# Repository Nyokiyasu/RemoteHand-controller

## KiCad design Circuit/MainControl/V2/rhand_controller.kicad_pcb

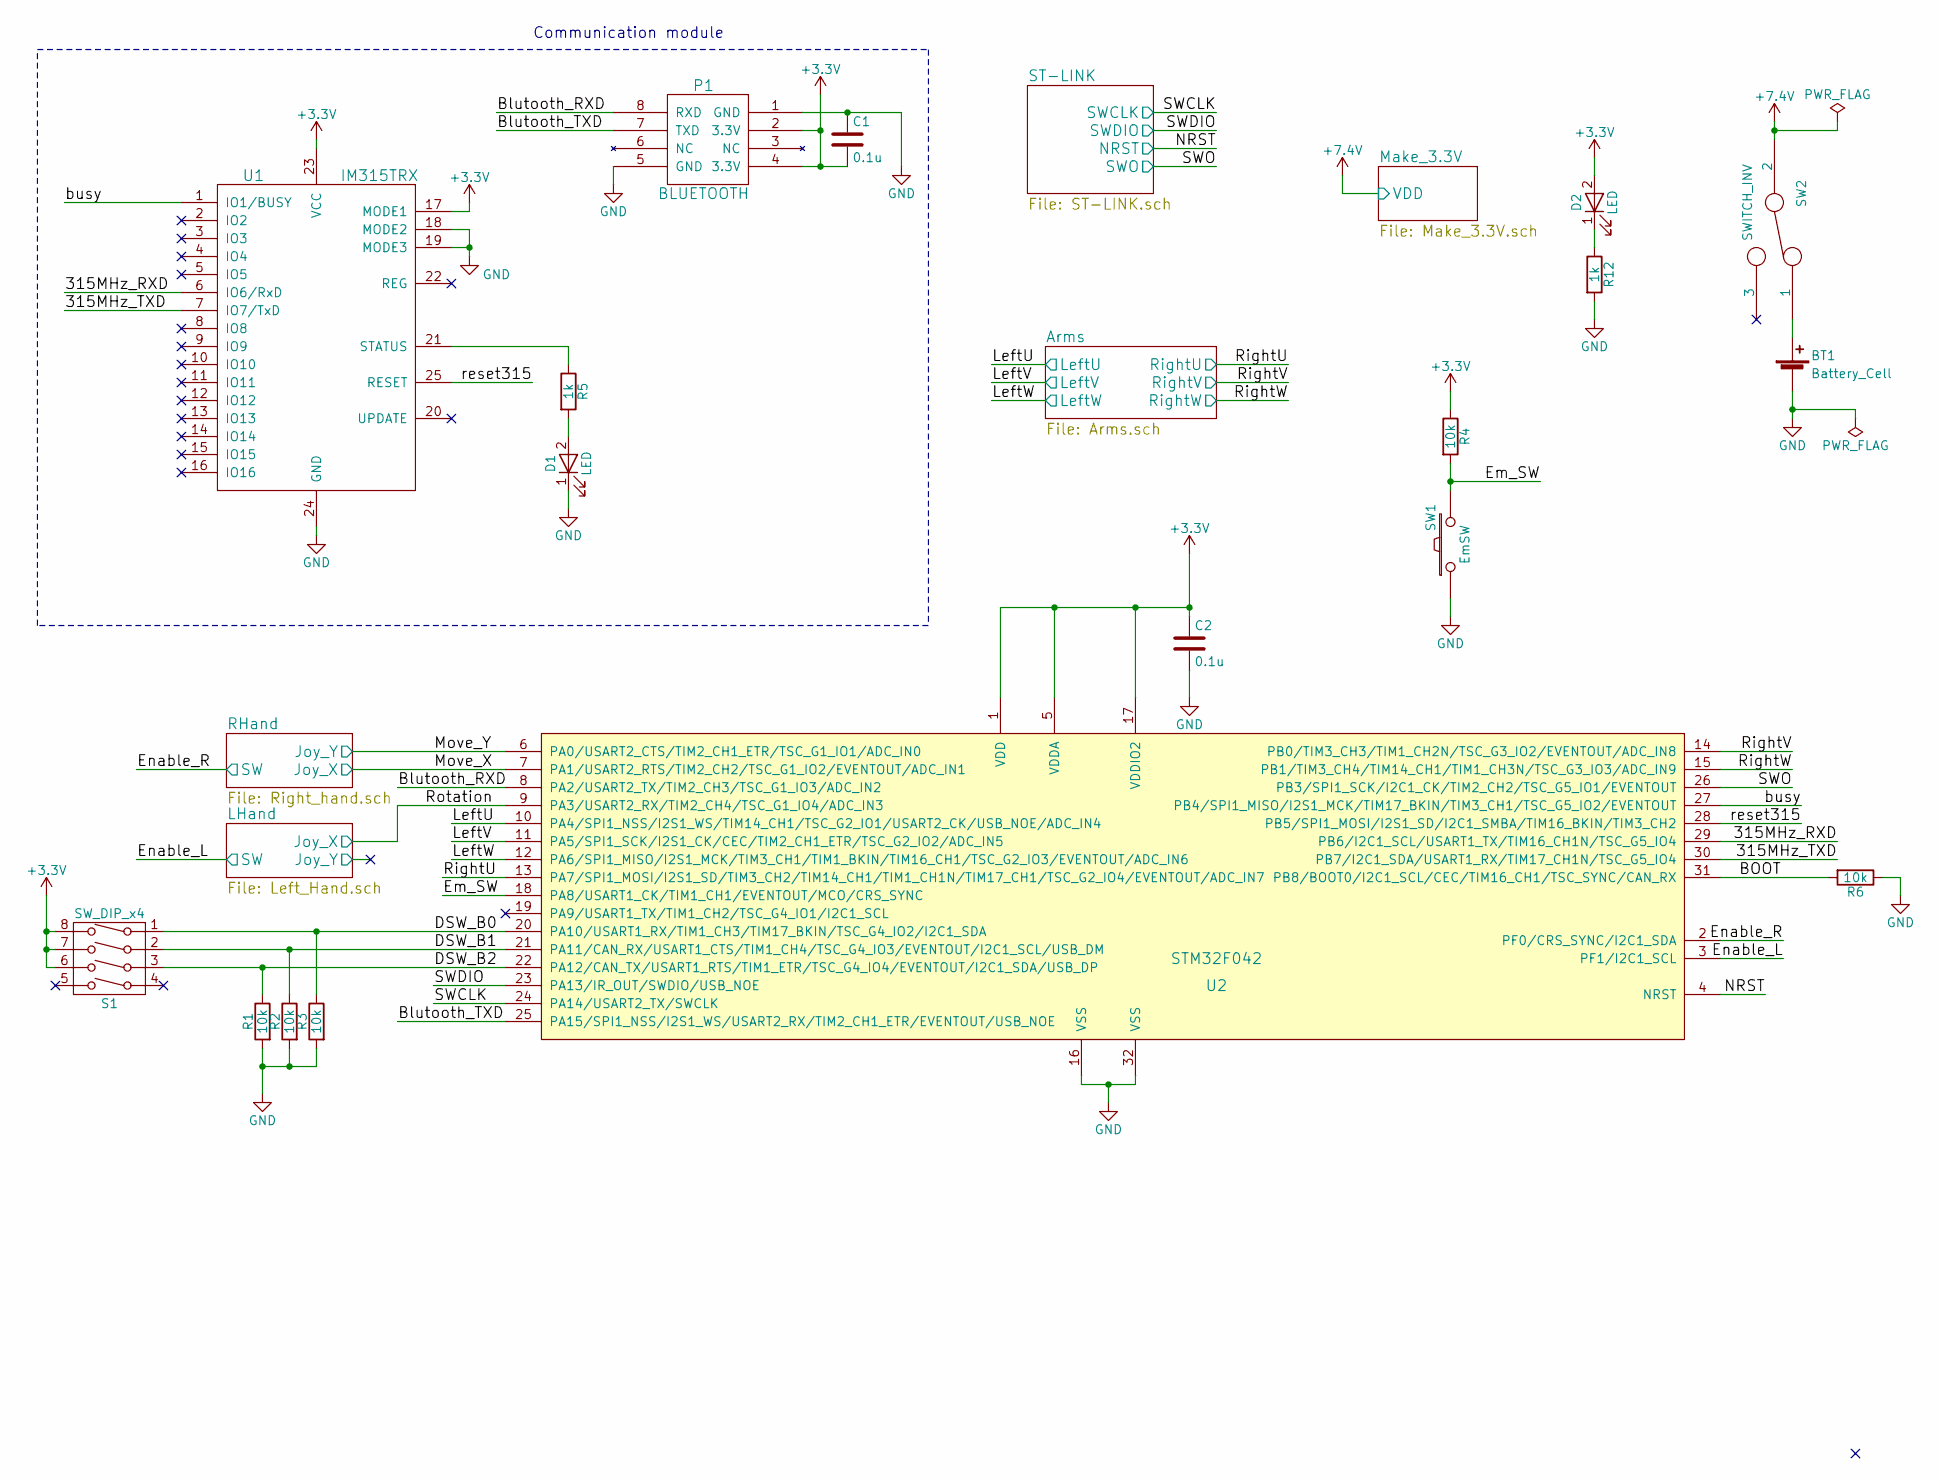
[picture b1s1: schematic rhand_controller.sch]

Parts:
BT1: Battery_Cell; XT_Mdot
C1, C2: 0.1u; C_0805_HandSoldering_LP
D1, D2: LED; LED_D5.0mm
P1: BLUETOOTH; ESD200
R1, R2, R3, R6: 10k; R_0603_HandSoldering_LP
R4: 10k; R_Axial_DIN0207_L6.3mm_D2.5mm_P7.62mm_Horizontal
R5, R12: 1k; R_Axial_DIN0207_L6.3mm_D2.5mm_P7.62mm_Horizontal
S1: SW_DIP_x4; SW_DIP_x4_W7.62mm_Slide
SW1: EmSW; XA_2Pin_LP
SW2: SWITCH_INV; _SW_TGR
U1: IM315TRX; IM315
U2: STM32F042; LQFP-32_7x7mm_Pitch0.8mm

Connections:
+3V3: C1.2, C2.1, D2.2 (A), P1.2 (3.3V), P1.4 (3.3V), R4.1, S1.6, S1.7, S1.8, U1.17 (MODE1), U1.23 (VCC), U2.1 (VDD), U2.5 (VDDA), U2.17 (VDDIO2); also elsewhere on the board
+7.4V: SW2.2; also elsewhere on the board
/315MHz_RXD: U1.6 (IO6/RxD), U2.29 (PB6/I2C1_SCL/USART1_TX/TIM16_CH1N/TSC_G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)
/315MHz_TXD: U1.7 (IO7/TxD), U2.30 (PB7/I2C1_SDA/USART1_RX/TIM17_CH1N/TSC_G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)
/BOOT: R6.2, U2.31 (PB8/BOOT0/I2C1_SCL/CEC/TIM16_CH1/TSC_SY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)
/Blutooth_RXD: P1.8 (RXD), U2.8 (PA2/USART2_TX/TIM2_CH3/TSC_G1_IO3/ADC_I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)
/Blutooth_TXD: P1.7 (TXD), U2.25 (PA15/SPI1_NSS/I2S1_WS/USART2_RX/TIM2_CH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)
/DSW_B0: R3.1, S1.1, U2.20 (PA10/USART1_RX/TIM1_CH3/TIM17_BKIN/TSC_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)
/DSW_B1: R2.1, S1.2, U2.21 (PA11/CAN_RX/USART1_CTS/TIM1_CH4/TSC_G4_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)
/DSW_B2: R1.1, S1.3, U2.22 (PA12/CAN_TX/USART1_RTS/TIM1_ETR/TSC_G4_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)
/Em_SW: R4.2, SW1.2, U2.18 (PA8/USART1_CK/TIM1_CH1/EVENTOUT/MCO/CRS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)
/Enable_L: U2.3 (PF1/I2C1_SCL); also elsewhere on the board
/Enable_R: U2.2 (PF0/CRS_SYNC/I2C1_SDA); also elsewhere on the board
/LeftU: U2.10 (PA4/SPI1_NSS/I2S1_WS/TIM14_CH1/TSC_G2_I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); also elsewhere on the board
/LeftV: U2.11 (PA5/SPI1_SCK/I2S1_CK/CEC/TIM2_CH1_ETR/T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); also elsewhere on the board
/LeftW: U2.12 (PA6/SPI1_MISO/I2S1_MCK/TIM3_CH1/TIM1_BK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); also elsewhere on the board
/Move_X: U2.7 (PA1/USART2_RTS/TIM2_CH2/TSC_G1_IO2/EVEN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); also elsewhere on the board
/Move_Y: U2.6 (PA0/USART2_CTS/TIM2_CH1_ETR/TSC_G1_IO1/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); also elsewhere on the board
/NRST: U2.4 (NRST); also elsewhere on the board
/RightU: U2.13 (PA7/SPI1_MOSI/I2S1_SD/TIM3_CH2/TIM14_CH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); also elsewhere on the board
/RightV: U2.14 (PB0/TIM3_CH3/TIM1_CH2N/TSC_G3_IO2/EVENT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); also elsewhere on the board
/RightW: U2.15 (PB1/TIM3_CH4/TIM14_CH1/TIM1_CH3N/TSC_G3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); also elsewhere on the board
/Rotation: U2.9 (PA3/USART2_RX/TIM2_CH4/TSC_G1_IO4/ADC_I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); also elsewhere on the board
/SWCLK: U2.24 (PA14/USART2_TX/SWCLK); also elsewhere on the board
/SWDIO: U2.23 (PA13/IR_OUT/SWDIO/USB_NOE); also elsewhere on the board
/SWO: U2.26 (PB3/SPI1_SCK/I2C1_CK/TIM2_CH2/TSC_G5_IO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); also elsewhere on the board
/busy: U1.1 (IO1/BUSY), U2.27 (PB4/SPI1_MISO/I2S1_MCK/TIM17_BKIN/TIM3_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)
/reset315: U1.25 (RESET), U2.28 (PB5/SPI1_MOSI/I2S1_SD/I2C1_SMBA/TIM16_B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)
GND: BT1.2 (-), C1.1, C2.2, D1.1 (K), P1.1 (GND), P1.5 (GND), R1.2, R2.2, R3.2, R6.1, R12.2, SW1.1, U1.18 (MODE2), U1.19 (MODE3), U1.24 (GND), U2.16 (VSS), U2.32 (VSS); also elsewhere on the board
unnamed: BT1.1 (+), SW2.1
unnamed: D1.2 (A), R5.2
unnamed: D2.1 (K), R12.1
unnamed: R5.1, U1.21 (STATUS)

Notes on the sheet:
Communication module

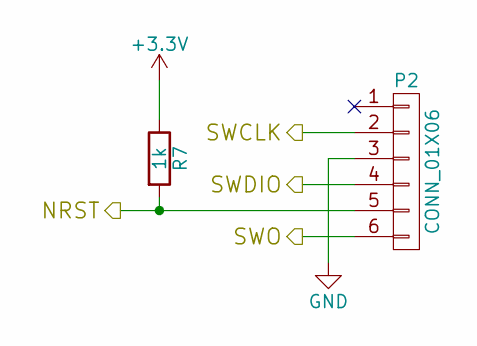
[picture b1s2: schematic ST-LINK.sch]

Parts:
P2: CONN_01X06; Pin_Header_Straight_1x06_Pitch2.54mm
R7: 1k; R_Axial_DIN0207_L6.3mm_D2.5mm_P7.62mm_Horizontal

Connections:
+3V3: R7.1; also elsewhere on the board
/NRST: P2.5, R7.2; also elsewhere on the board
/SWCLK: P2.2; also elsewhere on the board
/SWDIO: P2.4; also elsewhere on the board
/SWO: P2.6; also elsewhere on the board
GND: P2.3; also elsewhere on the board

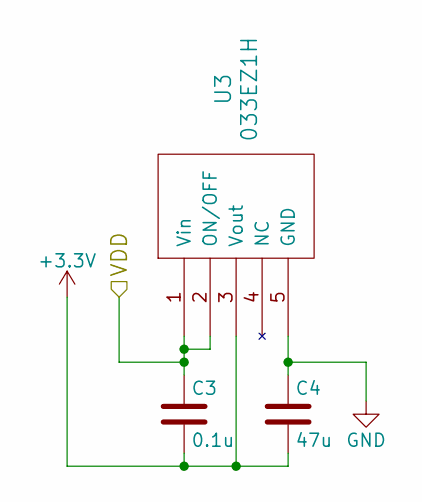
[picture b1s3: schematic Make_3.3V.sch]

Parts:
C3: 0.1u; C_0805_HandSoldering
C4: 47u; C_1210_HandSoldering
U3: 033EZ1H; PQ033EZ1HZ

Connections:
+3V3: C3.2, C4.2, U3.3 (Vout); also elsewhere on the board
+7.4V: C3.1, U3.1 (Vin), U3.2 (ON/OFF); also elsewhere on the board
GND: C4.1, U3.5 (GND); also elsewhere on the board

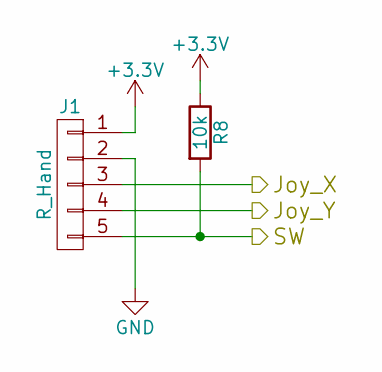
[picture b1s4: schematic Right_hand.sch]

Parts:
J1: R_Hand; XA_5Pin_LP
R8: 10k; R_Axial_DIN0207_L6.3mm_D2.5mm_P7.62mm_Horizontal

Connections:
+3V3: J1.1, R8.1; also elsewhere on the board
/Enable_R: J1.5, R8.2; also elsewhere on the board
/Move_X: J1.3; also elsewhere on the board
/Move_Y: J1.4; also elsewhere on the board
GND: J1.2; also elsewhere on the board

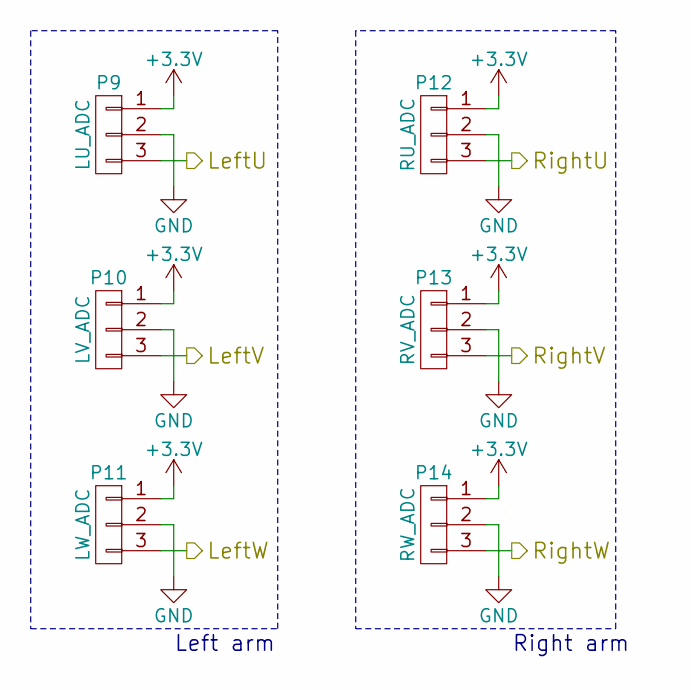
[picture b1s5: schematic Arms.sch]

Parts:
P9: LU_ADC; XA_3Pin_LP
P10: LV_ADC; XA_3Pin_LP
P11: LW_ADC; XA_3Pin_LP
P12: RU_ADC; XA_3Pin_LP
P13: RV_ADC; XA_3Pin_LP
P14: RW_ADC; XA_3Pin_LP

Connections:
+3V3: P9.1, P10.1, P11.1, P12.1, P13.1, P14.1; also elsewhere on the board
/LeftU: P9.3; also elsewhere on the board
/LeftV: P10.3; also elsewhere on the board
/LeftW: P11.3; also elsewhere on the board
/RightU: P12.3; also elsewhere on the board
/RightV: P13.3; also elsewhere on the board
/RightW: P14.3; also elsewhere on the board
GND: P9.2, P10.2, P11.2, P12.2, P13.2, P14.2; also elsewhere on the board

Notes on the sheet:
Right arm
Left arm

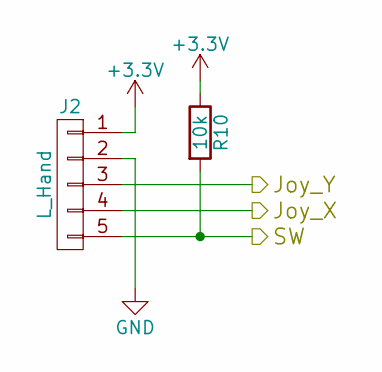
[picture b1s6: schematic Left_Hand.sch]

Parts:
J2: L_Hand; XA_5Pin_LP
R10: 10k; R_Axial_DIN0207_L6.3mm_D2.5mm_P7.62mm_Horizontal

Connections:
+3V3: J2.1, R10.1; also elsewhere on the board
/Enable_L: J2.5, R10.2; also elsewhere on the board
/LHand/Joy_Y: J2.3
/Rotation: J2.4; also elsewhere on the board
GND: J2.2; also elsewhere on the board

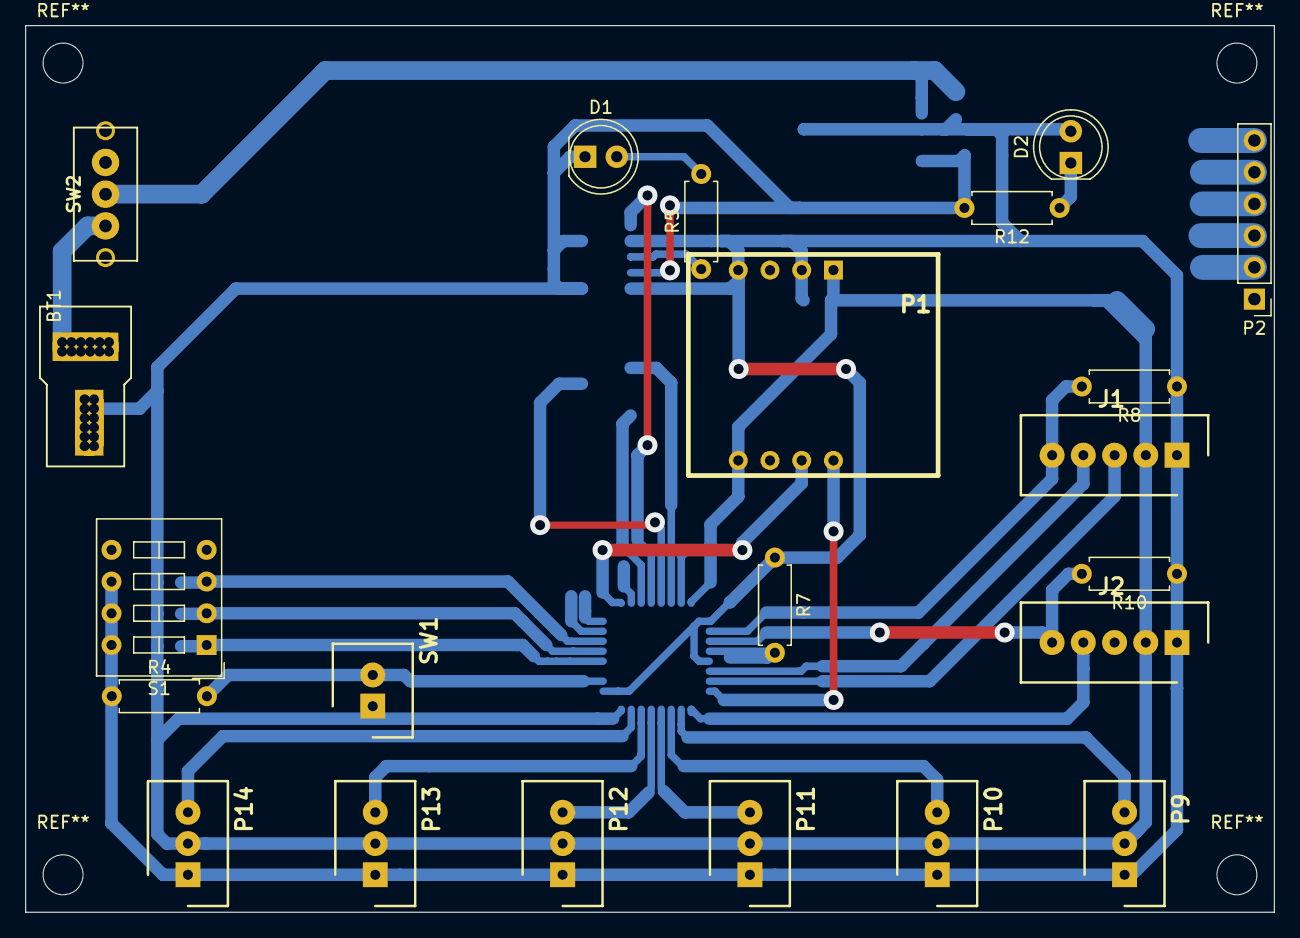
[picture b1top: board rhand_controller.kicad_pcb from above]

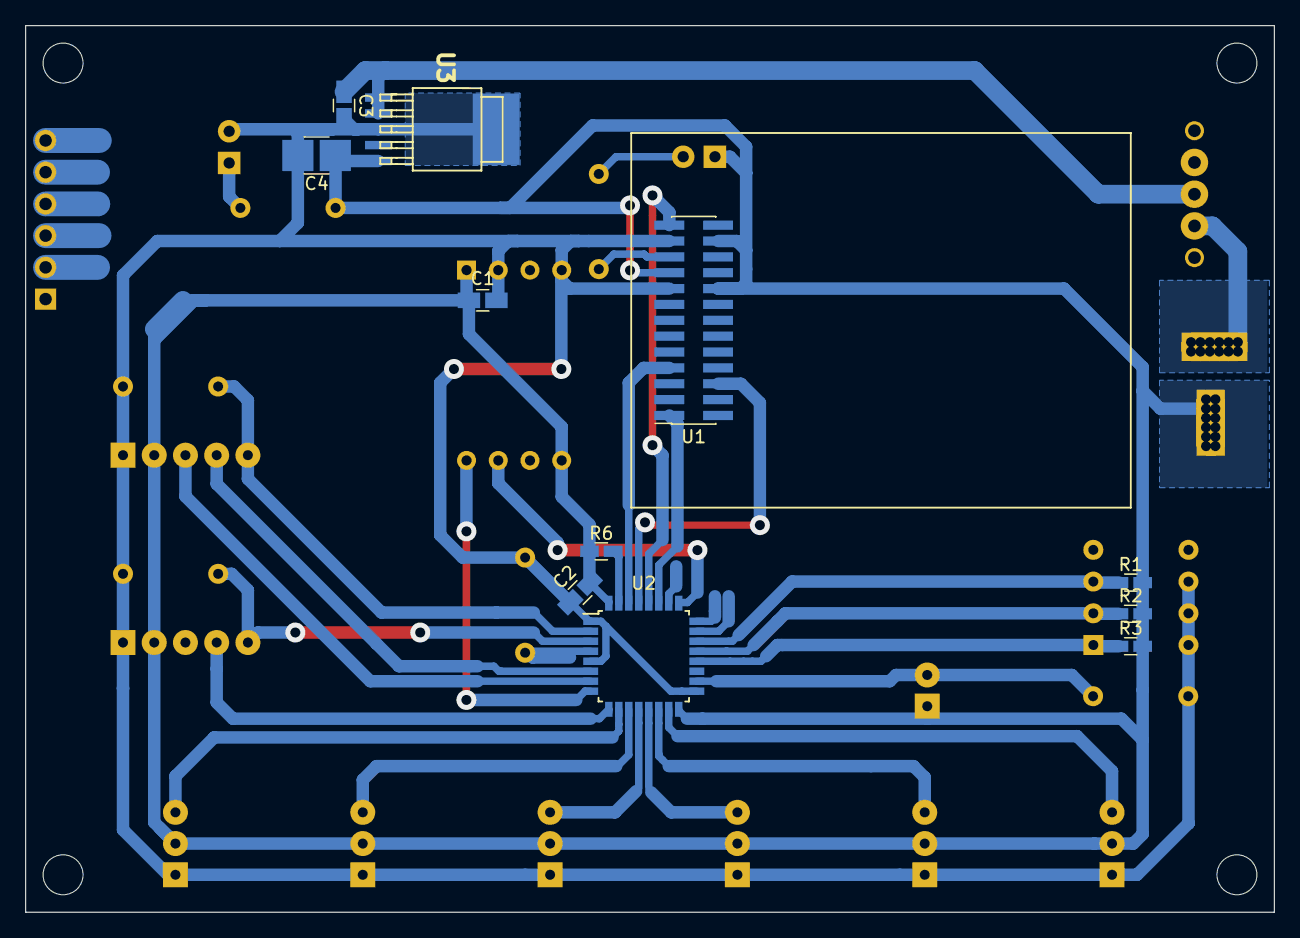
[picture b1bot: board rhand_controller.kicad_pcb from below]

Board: 2 copper layers, 100.0 x 71.0 mm, 33 parts (11 on the bottom side), 33 nets.

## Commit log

2017-06-06 基板作成の下地
2017-06-06 回路図ほぼ完成
2017-06-07 315MHzモジュールなどの追加
2017-06-07 未配線の追加
2017-06-07 部品の割り付け
2017-06-07 ライブラリの変更
2017-06-08 機能の追加
2017-06-10 何を変えたか忘れたけど更新
2017-06-10 シートわけ
2017-06-11 シート分けと移動
2017-06-12 回路図の配置変更
2017-06-13 回路図完成
2017-06-14 実態配線図書き始め
2017-06-15 特になし
2017-06-15 部品割り付けの完了
2017-06-15 部品を基板上へ適当に配置
2017-06-16 ピンヘッダを表面実装へ
2017-06-16 ADCのピン配置修正と配線引きはじめ
2017-06-18 あらかた終わったぞ
2017-06-19 IM315の位置変更
2017-06-19 作業しようと思ったらほとんどできなかった
2017-06-20 IM315のLEDの配線変更
2017-06-21 実態配線図完了
2017-06-21 SWDのジャンパ用配線の追加とガーバーデータの作製
2017-07-01 プロジェクトの作成
2017-07-01 DipSWの読み取り関数を追加
2017-07-01 プロトタイプ宣言とBlutoothアドレス
2017-07-01 ファイルネームの変更とヘッダファイルの作成
2017-07-01 Bluetoothのinitを追加
2017-07-01 IM315の初期化を追加
2017-07-01 文字列を送信する関数の作成
2017-07-02 USARTの文字列送信関数の作成
2017-07-05 IM315の8Byte送信関数を作成
2017-07-06 手元のSWの初期化関数を追加
2017-07-07 Bluetoothで用いるUSARTでPCと通信できた
2017-07-11 USART受信用の関数等定義
2017-07-15 Bluetoothの通信成功
2017-07-15 IM315と通信可能の時のみ送信するように変更
2017-07-15 送信完了を検知するよう変更
2017-07-15 ADCがわかんねえ
2017-07-17 IM315のデバッグ完了
2017-07-17 ADC初期化のひな型完成
2017-07-17 変更なし
2017-07-17 DMAのデバッグ待ち
2017-07-17 sysconfigにもDMAの設定あるから要注意
2017-07-20 チャンネル選択とサンプリングレートの初期化
2017-07-20 ADCの値を一つのチャンネルで取得することに成功
2017-07-20 ADC送信できた
2017-07-20 ミスった
2017-07-20 基本的な機能(データの取得と送信)の完成
2017-07-20 非常停止スイッチの初期化
2017-07-21 コメントとデータ取得のバグ修正
2017-07-21 Enableの機能追加とRHC構造体から非常停止のメンバ削除
2017-07-25 基板側のADCポートの定義追加
2017-07-25 基板側のセンサの名前付けに対応
2017-07-26 構造体->共用体
2017-07-26 送信するフレームが8Byteのままだったため16Byteに修正
2017-07-28 STMstudioでデバッグするように色々追加
2017-07-29 ファイル構造の変更
2017-07-29 変更点がわかんないんだよなあ
2017-08-02 includeの仕方を変更
2017-08-07 ジョイスティック固定用の作成
2017-08-08 穴の配置はたぶん合ってる
2017-08-08 STLファイルをレポジトリに追加しないようにした
2017-08-08 --allow-empty-message
2017-08-08 基板固定用の穴と三端子レギュレータ回りの配線の変更
2017-08-08 merged
2017-08-09 ガーバー出力
2017-08-09 ジョイスティックの作成
2017-08-09 メイン基板の変更とジョイスティック固定用基板の作成
2017-08-22 ねじ穴付けた
2017-08-22 ジョイスティック固定威容の基板外形を円形へ変更
2017-08-22 固定用の穴追加
2017-08-22 数値確認用の従動寸法を追加
2017-08-23 持つところの設計
2017-08-23 フォルダ構造の変更
2017-08-24 Ver.2の設計開始
2017-08-25 配置をちょっとした
2017-08-28 ラベル名のつけ方変更
2017-08-28 3Dプリンタで出力するための細かい変更
2017-08-28 配線が半分完了,電源と無線モジュールが未配線
2017-08-29 コミット編集しようとしたら全部破棄されたからやる気失った
2017-09-01 回路設計完了
2017-09-01 底面の追加
2017-09-04 ケーブル径と結束バンド
2017-09-07 ADCの初期化変更
2017-09-07 回転をジョイスティックに変更したことによる関数の修正
2017-09-11 コントローラ単体でのデバッグ完了
2017-09-14 プログラムの整理
2017-09-27 遅延の原因がわからない
2017-09-27 めんどくさいやつのやつ
2017-09-27 遅延の原因はBluetoothモジュールのバッファ
2017-10-13 コネクト直後に変な信号が入るみたいなので対策
2017-10-14 センサ取得関数が間違ってた
